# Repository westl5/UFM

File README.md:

# UFM - Unidentified Flying Mouse
**McMaster University Electrical & Computer Engineering Capstone Team 10**

## Project Overview
UFM (Unidentified Flying Mouse) is a wrist-worn computer input device designed for individuals with limited hand dexterity, those who have undergone hand amputation, or those who were born without a hand. The system converts movements from the arm to mouse functions and sends mouse commands to the user's PC over bluetooth. 

## Project Video
https://github.com/user-attachments/assets/12428ccc-8710-40ed-a4b3-f343b9fc400c

([Full Video](https://youtu.be/52ZPP2TyDK4))

## Team Members
- Luke West ([@westl5](https://github.com/westl5))
- George Gill ([@georgegill](https://github.com/georgegill))
- Matthew Yu ([matthyu2002](https://github.com/matthyu2002))
- Ryan Xu ([@RyanXu02](https://github.com/RyanXu02))
  
## Contact
For more information about the UFM project, please contact any of the team members listed above.

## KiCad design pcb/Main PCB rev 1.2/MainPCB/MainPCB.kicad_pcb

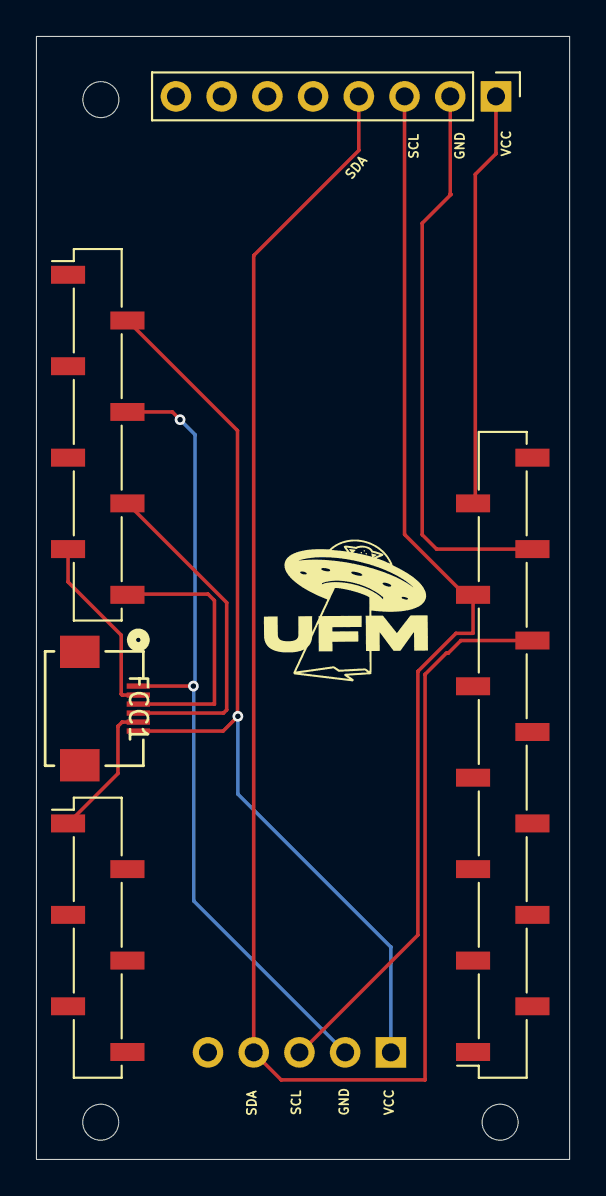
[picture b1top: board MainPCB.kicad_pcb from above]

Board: 2 copper layers, 29.6 x 62.4 mm, 6 parts (1 on the bottom side), 8 nets.

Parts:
BotLeft1: Conn_01x06; PinSocket_1x06_P2.54mm_Vertical_SMD_Pin1Left
FCC1: Conn_01x06; CONN_XF3M-0615-1B_OMR
MDVRCONN1: Conn_01x04; PinHeader_1x05_P2.54mm_Vertical
MPUCONN1: Conn_01x04; PinHeader_1x08_P2.54mm_Vertical
RightSide1: Conn_01x14; PinSocket_1x14_P2.54mm_Vertical_SMD_Pin1Right
Topleft1: Conn_01x08; PinSocket_1x08_P2.54mm_Vertical_SMD_Pin1Left

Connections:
/CSB: BotLeft1.1, FCC1.5
/GND: FCC1.1, MDVRCONN1.2, MPUCONN1.2, RightSide1.12, Topleft1.4
/MISO: FCC1.3, Topleft1.8
/MOSI: FCC1.2, Topleft1.7
/SCK: FCC1.4, Topleft1.6
/SCL: MDVRCONN1.3, MPUCONN1.3, RightSide1.11
/SDA: MDVRCONN1.4, MPUCONN1.4, RightSide1.10
/VCC: FCC1.6, MDVRCONN1.1, MPUCONN1.1, RightSide1.13, Topleft1.2

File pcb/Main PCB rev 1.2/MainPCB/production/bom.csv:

Designator,Footprint,Quantity,Value,LCSC Part #
"_3, _2, ",,3,,
BOTLEFT1,PinSocket_1x06_P2.54mm_Vertical_SMD_Pin1Left,1,Conn_01x06,
FCC1,CONN_XF3M-0615-1B_OMR,1,Conn_01x06,
MDVRCONN1,PinHeader_1x05_P2.54mm_Vertical,1,Conn_01x04,
MPUCONN1,PinHeader_1x08_P2.54mm_Vertical,1,Conn_01x04,
RIGHTSIDE1,PinSocket_1x14_P2.54mm_Vertical_SMD_Pin1Right,1,Conn_01x14,
TOPLEFT1,PinSocket_1x08_P2.54mm_Vertical_SMD_Pin1Left,1,Conn_01x08,

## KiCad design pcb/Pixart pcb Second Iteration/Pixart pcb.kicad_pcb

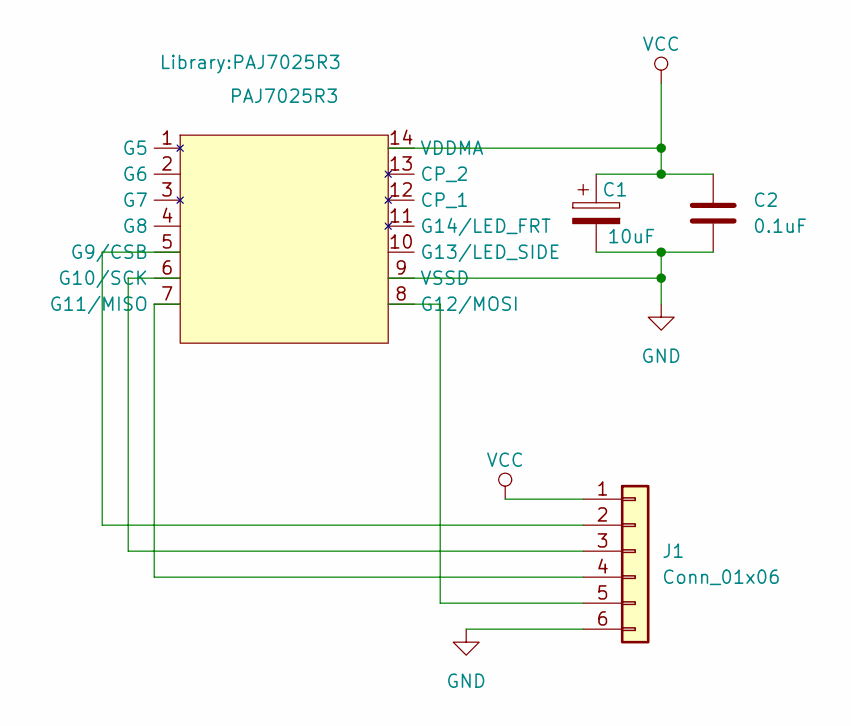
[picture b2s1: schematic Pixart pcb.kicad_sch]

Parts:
C1: 10uF; TAJA106K016RNJ 10uF
C2: 0.1uF; GRM155R71C104KA88D 0.1uF
J1: Conn_01x06; Molex_KK-6410-06_06x2.54mm_Straight
PAJ7025R3: PAJ7025R3

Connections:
GND: C1.2, C2.2, J1.6, PAJ7025R3.9 (VSSD)
unnamed: J1.2, PAJ7025R3.5 (G9/CSB)
unnamed: J1.3, PAJ7025R3.6 (G10/SCK)
unnamed: J1.4, PAJ7025R3.7 (G11/MISO)
unnamed: J1.5, PAJ7025R3.8 (G12/MOSI)
VCC: C1.1, C2.1, J1.1, PAJ7025R3.14 (VDDMA)

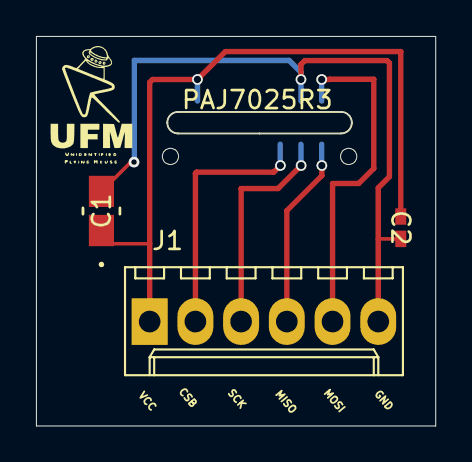
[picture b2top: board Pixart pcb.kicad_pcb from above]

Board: 2 copper layers, 22.2 x 21.6 mm, 4 parts (0 on the bottom side), 6 nets.

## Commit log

2024-12-28 added files via upload
2024-12-28 changed includes to use new directory structure
2025-01-04 deleted trzy code, added python sim code
2025-01-04 removed .vscode file
2025-01-06 general cleanup of test_pnp.opencv.py
2025-01-06 removed unused functions in test_pnp_opencv.py
2025-01-06 updated test_pnp_opencv.py
2025-01-07 added code for imu rotation tests
2025-01-08 added print_sensor.ino from trzy, added detailed comments
2025-01-08 added more commenting to print_sensor.ino
2025-01-08 updated print_sensor.ino in debugging process
2025-01-09 updated print_sensor.ino for debugging
2025-01-09 remove print_settings line in loop
2025-01-11 updating simulation for pose estimation
2025-01-11 changed test_pnp_opencv_.py
2025-01-12 PIXART sensor pcb
2025-01-15 updated simulation
2025-01-16 Pixart PCB Second Iteration
2025-01-16 deleted visualize_leds, updated test_pnp
2025-01-17 updated simulation by adding point ordering check, still wip
2025-01-17 added files from pixartDebug to main repo
2025-01-17 reorganized folders
2025-01-17 added directory for documents
2025-01-17 added datasheets
2025-01-17 fixed name for mpu6050 datasheet
2025-01-18 added 2d visual test video, and image of LED setup
2025-01-18 added pixart breadbord photo to docs
2025-01-18 added report and photos
2025-01-21 added more photos
2025-01-27 updated docs
2025-01-27 updated pixartDebug
2025-01-28 made new code to get position of camera in 3d space using pixart data
2025-01-28 better serial read method, code is now functional
2025-01-28 pnp code now functional, and updated faster serial read method
2025-01-28 testing pyqt graphing instead of matlab
2025-02-03 updated python code
2025-02-21 init commit for firebeetle app with old esp src code
2025-02-21 setup vs proj for the host app
2025-02-25 added mouse cursor code, added to docs and pcb folders
2025-02-25 working serial monitor
2025-02-25 added alternative option for cursor with pattern matching in pixart_cursor.py
2025-02-25 fixed get_points function by changing tuple format
2025-02-26 added ble test to main to start testing moving mouse using esp32
2025-03-05 hostapp cursor movement
2025-03-05 firebeetle software added mouse functionalities
2025-03-05 firebeeltle platformio project lib dependencies
2025-03-05 esp code dont print settings when initializing
2025-03-05 added gitignore
2025-03-05 updated gitignore
2025-03-05 fixed updated git ignore
2025-03-05 python cursor code fix
2025-03-05 junk in hostapp
2025-03-05 cleaned up gitignore files that were already in the repo
2025-03-05 cleaned up gitignore in pixart debug
2025-03-05 added homography computations to main.cpp
2025-03-05 updated firebeetle gitignore
2025-03-05 updated focal length and cx,cy values
2025-03-11 Main PCB
2025-03-11 basic debug flash
2025-03-11 added ble mouse to old debug project
2025-03-11 changed nothing
2025-03-11 dont print debug
2025-03-11 cleaned up unused code blocks, added ble mouse
2025-03-11 mouse movement
2025-03-12 added blk & wht ufm logos w/ clear background
2025-03-16 added logo with blue text, renamed logo files
2025-03-20 WORKING BLUETOOTH MOUSE
2025-03-20 added poster ppt file and illustrations
2025-03-24 hold logic and direction change
2025-03-25 implemented click and cursor mode
2025-03-25 added motor driver package
2025-03-25 fixed clicked mode
2025-03-25 working vibrations
2025-03-26 added docs for poster and render video
2025-03-30 Cleaned up README.md
2025-03-30 Added some visuals and videos
2025-04-04 added segemnts of ufm logo and poster
2025-04-04 added vector for poster block diagram
2025-04-04 pdf and png versions of the poster block diagram
2025-04-04 added poster block diagram, no background versions
2025-04-04 added boundry detection
2025-04-07 added GUI for serial configuration and sensitivity control
2025-04-07 added serial command processing for sensitivity, handedness, and click mode configuration
2025-04-07 updated .gitignore to exclude internal build directories and user-specific files
2025-04-07 added UFMGUI assets and build
2025-04-07 updated .gitignore to exclude UFMGUI build directory
2025-04-07 added internal binaries and translations for UFMGUI
2025-04-08 Added UFM Video
2025-04-08 Update README.md with video
2025-04-08 Fixed Embeded Video
2025-04-08 Added Full video to readme
2025-04-08 Update README.md to use yt video instead of macvideo
2025-04-22 added final report
